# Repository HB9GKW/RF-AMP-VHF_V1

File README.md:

# RF-AMP-VHF_V1
2 Meter VHF LDMOS amplifier module:
- 1500W output power at 1dB compression 
- On-Board low-pass filter (5th order chebyshev)
- On-board directional coupler and temperature compensated forward / reflected detector
- Temperature measurement and BIAS stabilization
- RF input detector
- high-power 9:1 TLT

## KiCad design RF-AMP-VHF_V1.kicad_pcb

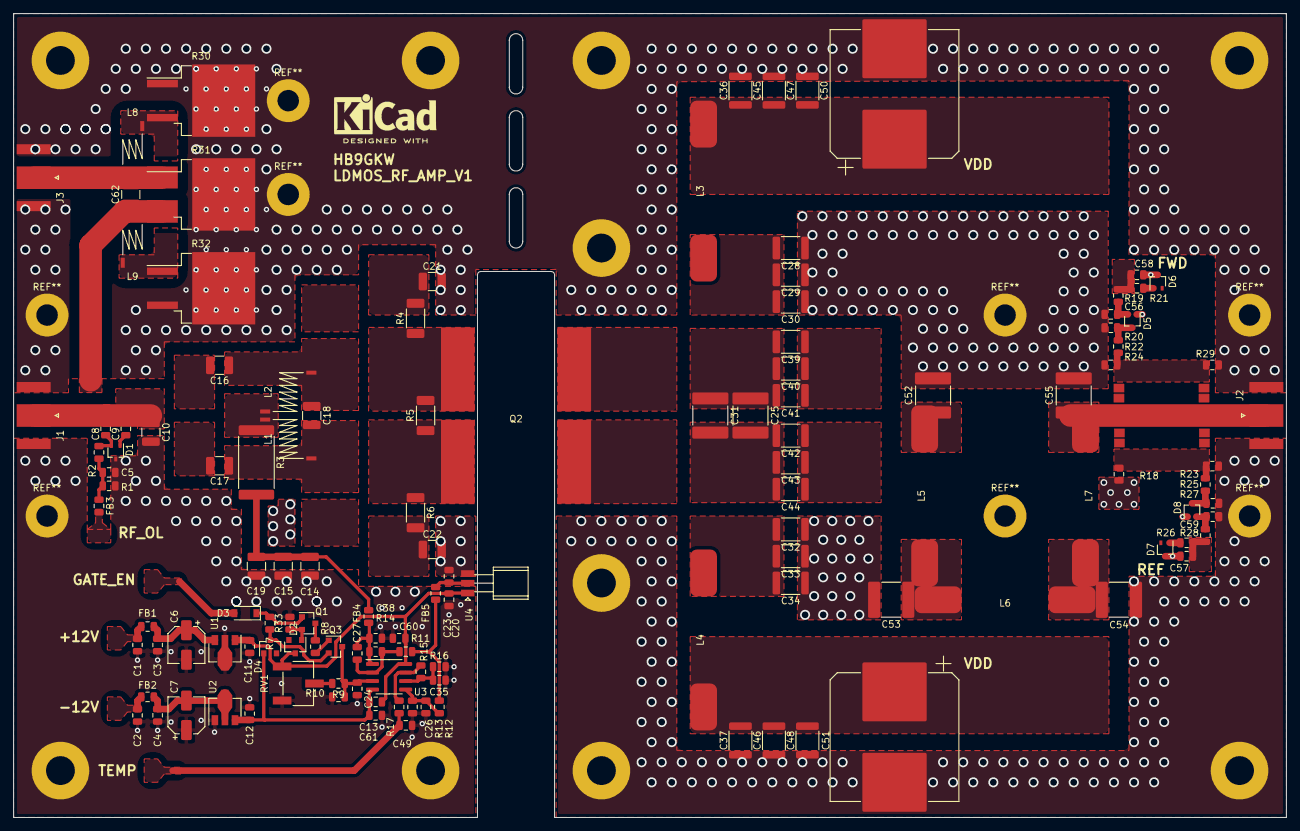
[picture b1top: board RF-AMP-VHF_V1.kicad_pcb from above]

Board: 2 copper layers, 190.0 x 120.0 mm, 128 parts (0 on the bottom side), 59 nets.

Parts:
C1, C2, C3, C4, C11, C12, C13, C20, C23, C26, C27, C35, C38, C49, C60, C61: 100n; C_0805_2012Metric
C5: 220p; C_0805_2012Metric
C6, C7: 10u; CP_Elec_5x5.7
C8, C9: 6p8; C_0805_2012Metric
C10: 1p8; C_1210_3225Metric
C14: 100n; C_1210_3225Metric
C15, C21, C22: 10n; C_1210_3225Metric
C16, C17, C19: 1n; C_1210_3225Metric
C18: 10p; C_1210_3225Metric
C24: 1n; C_0805_2012Metric
C25, C31: 15p; C_2220_5650Metric
C28, C29, C33, C34, C36, C37: 1n; C_1812_4532Metric
C30, C32, C39, C40, C41, C42, C43, C44: 470p; C_1812_4532Metric
C45, C46: 10n; C_1812_4532Metric
C47, C48: 100n; C_1812_4532Metric
C50, C51: 220u; CP_Elec_18x22
C52, C55: 1p8; C_2220_5650Metric
C53, C54: 27p; C_2220_5650Metric
C56, C57, C58, C59: 330p; C_0805_2012Metric
C62: 22p; C_1210_3225Metric
D1, D5, D6, D7, D8: BAT54SW; SOT-323_SC-70
D2, D4: BZX84C5V6; D_SOT-23_ANK
D3: 1N4148W; D_SOD-123
FB1, FB2, FB3, FB4, FB5: BLM21BD102; R_0805_2012Metric
J1: RF IN; SMA_Amphenol_132289_EdgeMount
J2: RF OUT; SMA_Amphenol_132289_EdgeMount
J3: RF IN ATT; SMA_Amphenol_132289_EdgeMount
L1, L2: 150n; L_Neosid_Air-Coil_SML_6-10turn_HDM0431A-HDM1031A
L3, L4: 330n; Air_Coil_1
L5, L7: 61n; Air_Coil_1
L6: 105n; Air_Coil_1
L8, L9: 22n; L_Neosid_Air-Coil_SML_3turn_HDM0331A
Q1: BC857; SOT-23
Q2: BLF189XRA; SOT-539
Q3: BC847; SOT-23
R1, R7, R19, R21, R26, R28, R33: 4k7; R_0805_2012Metric
R2: 470; R_0805_2012Metric
R3: 10; R_4020_10251Metric
R4, R6: 10; R_2010_5025Metric
R5: 50; R_2010_5025Metric
R8, R9: 47k; R_0805_2012Metric
R10, R12, R14, R16: 100k; R_0805_2012Metric
R11: 490k; R_0805_2012Metric
R13, R15: 220k; R_0805_2012Metric
R17: 330; R_0805_2012Metric
R18, R29: 51; R_0805_2012Metric
R20, R23, R24, R27: 100; R_0805_2012Metric
R22, R25: 68; R_0805_2012Metric
R30, R32: 100; TO-263-2
R31: 68; TO-263-2
RV1: 20k; Potentiometer_Bourns_3269W_Vertical
U1: L78L05_SOT89; SOT-89-3
U2: L79L05_SOT89; SOT-89-3
U3: LM7332; SOIC-8_3.9x4.9mm_P1.27mm
U4: TMP36GT9; TO-92_Inline_W4.0mm_Horizontal_FlatSideDown

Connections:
+5V: C11.1, C13.1, C20.1, C60.1, D2.1, RV1.1, U1.1, U3.8, U4.1
+12V: C1.1, FB1.2
-5V: C12.1, C13.2, C61.1, D4.2, U2.3, U3.4
-12V: C2.1, FB2.2
Earth: C1.2, C2.2, C3.2, C4.2, C5.2, C6.2, C7.1, C10.2, C11.2, C12.2, C14.2, C15.2, C19.2, C20.2, C21.2, C22.2, C23.2, C24.2, C26.2, C28.1, C29.1, C30.1, C32.1, C33.1, C34.1, C35.2, C36.2, C37.2, C38.2, C45.2, C46.2, C47.2, C48.2, C49.2, C50.2, C51.2, C52.2, C53.2, C54.2, C55.2, C56.2, C57.2, C58.2, C59.2, C60.2, C61.2, D1.3, D5.1, D6.3, D7.3, D8.1, J1.2, J2.2, J3.2, Q2.5, R1.2, R10.2, R13.2, R16.2, R18.2, R20.2, R23.2, R24.2, R27.2, R29.2, R30.1, R30.2, R31.2, R32.2, R32.3, R33.2, RV1.3, U1.2, U2.1, U4.3
FWD: C58.1, R19.2, R21.1
GATE: C14.1, C15.1, C19.1, FB4.1, R3.2
unnamed: C3.1, C6.1, FB1.1, U1.3
unnamed: C4.1, C7.2, FB2.1, U2.2
unnamed: C5.1, FB3.1, R1.1, R2.2
unnamed: C8.2, D1.2, R2.1
unnamed: C9.2, D1.1
unnamed: C8.1, C9.1, C10.1, J1.1
unnamed: C16.1, C18.1, L2.2
unnamed: C17.1, C18.2, L1.1
unnamed: C21.1, R4.2
unnamed: C22.1, R6.2
unnamed: C23.1, FB5.1, U4.2
unnamed: C24.1, Q3.3, R9.1, R10.1, U3.3
unnamed: C25.1, C31.1, C39.2, C40.2, C41.2
unnamed: C25.2, C31.2, C42.2, C43.2, C44.2
unnamed: C26.1, R12.1, R13.1, U3.5
unnamed: C27.1, C38.1, FB4.2, R14.1, U3.1
unnamed: C27.2, R11.1, R14.2, U3.2
unnamed: C28.2, C29.2, C30.2, L4.1, Q2.2
unnamed: C32.2, C33.2, C34.2, L3.2, Q2.1
unnamed: C35.1, R15.2, R16.1, U3.6
unnamed: C39.1, C40.1, C41.1
unnamed: C42.1, C43.1, C44.1
unnamed: C52.1, L5.1
unnamed: C53.1, L5.2, L6.1
unnamed: C54.1, L6.2, L7.1
unnamed: C55.1, J2.1, L7.2
unnamed: C56.1, D5.2, R19.1
unnamed: C59.1, D8.2, R28.1
unnamed: C62.1, L9.1, R31.3
unnamed: C62.2, J3.1, L8.1, R31.1
unnamed: D2.2, Q1.2, R33.1
unnamed: D3.1, Q1.1, R7.2
unnamed: D4.1, Q3.2, R7.1
unnamed: D5.3, R20.1, R22.2
unnamed: D6.1, R21.2
unnamed: D7.1, R26.2
unnamed: D8.3, R25.1, R27.1
unnamed: FB5.2, R11.2, R12.2
unnamed: L1.2, L2.1, R3.1
unnamed: L8.2, R30.3
unnamed: L9.2, R32.1
unnamed: Q1.3, R8.2
unnamed: Q2.3, R4.1, R5.2
unnamed: Q2.4, R5.1, R6.1
unnamed: Q3.1, R8.1
unnamed: R9.2, RV1.2
unnamed: R15.1, R17.2, U3.7
unnamed: R18.1, R23.1, R25.2
unnamed: R22.1, R24.1, R29.1
REF: C57.1, R26.1, R28.2
TEMP: C49.1, R17.1
VDD: C36.1, C37.1, C45.1, C46.1, C47.1, C48.1, C50.1, C51.1, L3.1, L4.2

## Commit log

2020-01-13 changing gerber format
2020-01-14 Review 1
2020-01-18 prototype release
2020-01-19 added BOM
2020-02-04 bug fixes
2020-02-05 schematic update
2020-02-07 prototype improvements
